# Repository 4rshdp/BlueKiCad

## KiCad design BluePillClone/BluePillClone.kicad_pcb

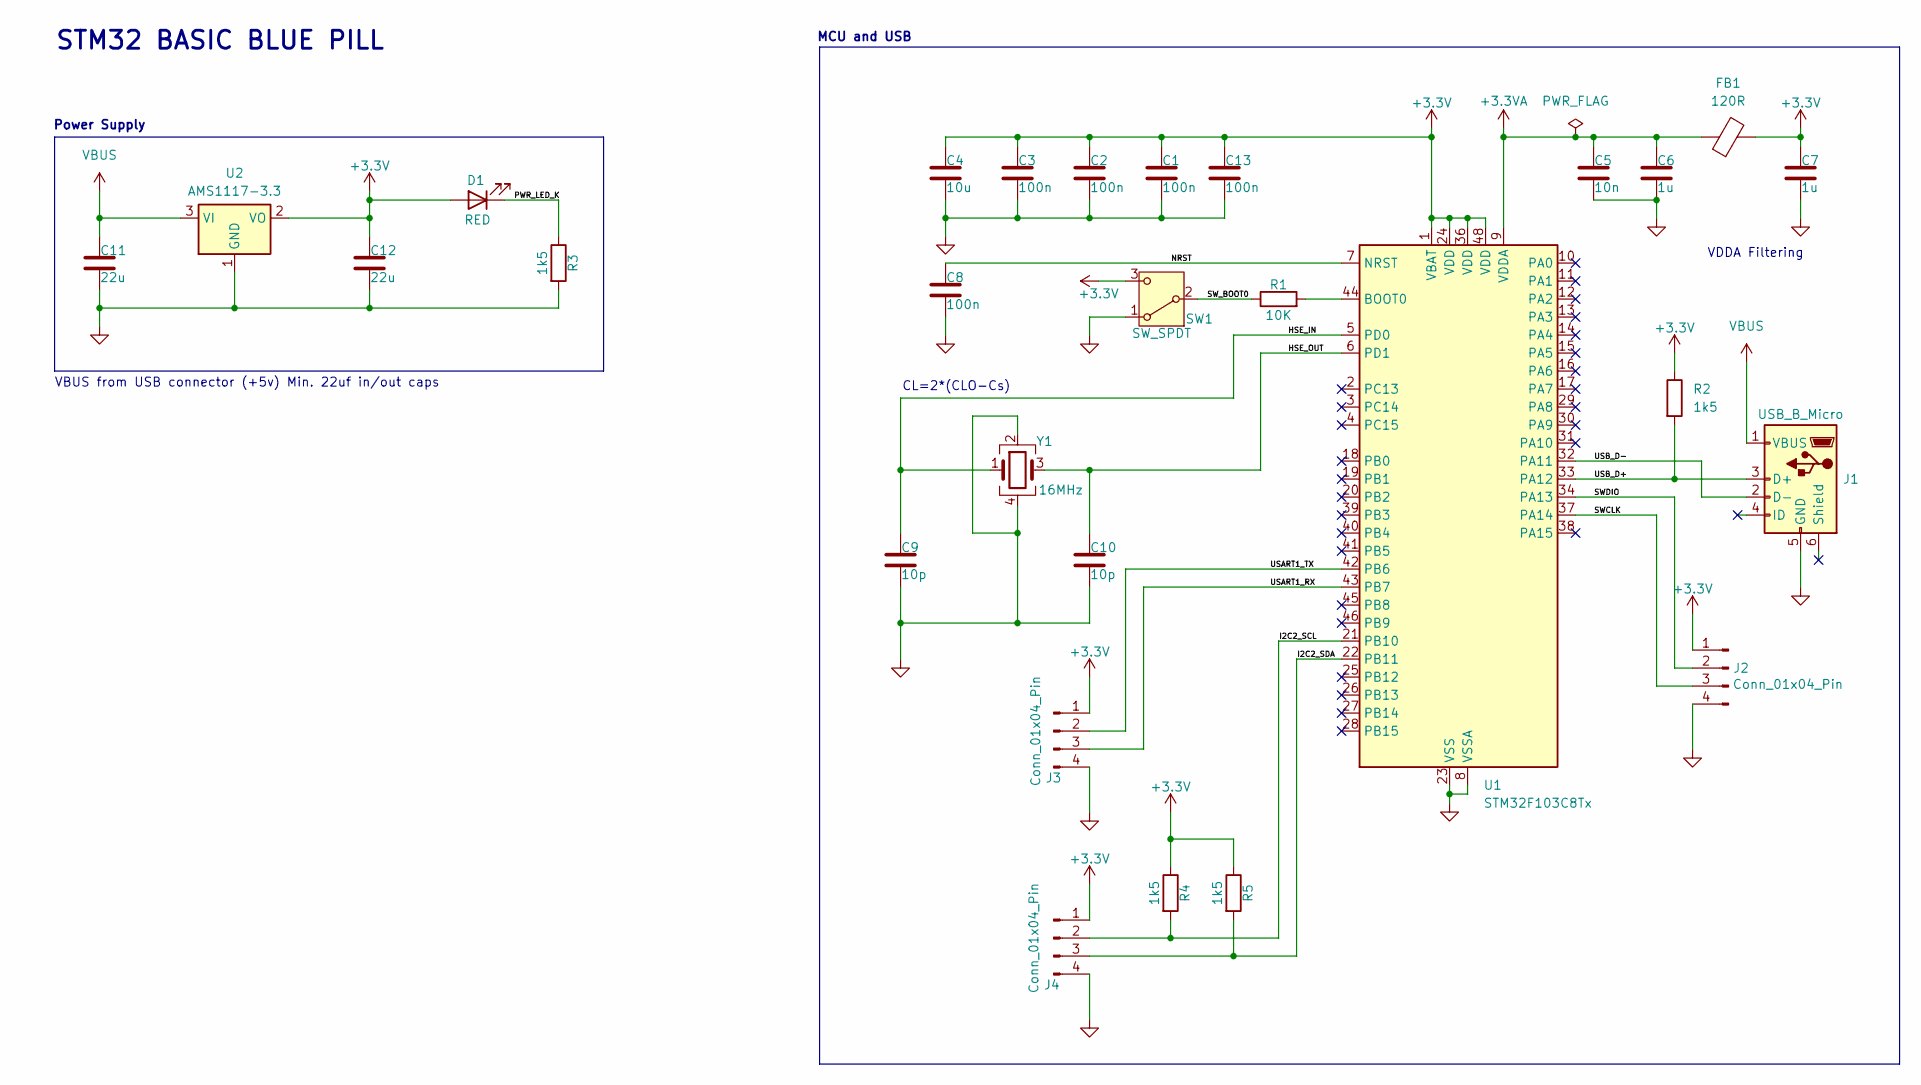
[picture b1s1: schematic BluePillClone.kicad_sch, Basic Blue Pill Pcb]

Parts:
C1, C2, C3, C8, C13: 100n; C_0402_1005Metric
C4: 10u; C_0402_1005Metric
C5: 10n; C_0402_1005Metric
C6, C7: 1u; C_0402_1005Metric
C9, C10: 10p; C_0402_1005Metric
C11, C12: 22u; C_0805_2012Metric
D1: RED; LED_0603_1608Metric
FB1: 120R; L_0603_1608Metric
J1: USB_B_Micro; USB_Micro-B_Wuerth_629105150521
J2, J3, J4: Conn_01x04_Pin; PinHeader_1x04_P2.54mm_Vertical
R1: 10K; R_01005_0402Metric
R2, R3, R4, R5: 1k5; R_01005_0402Metric
SW1: SW_SPDT; SW_Push_1P2T_Vertical_E-Switch_800UDP8P1A1M6
U1: STM32F103C8Tx; LQFP-48_7x7mm_P0.5mm
U2: AMS1117-3.3; SOT-223-3_TabPin2
Y1: 16MHz; Crystal_SMD_3225-4Pin_3.2x2.5mm

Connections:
+3.3V: C1.1, C2.1, C3.1, C4.1, C7.1, C12.1, C13.1, D1.2 (A), FB1.2, J2.1, J3.1, J4.1, R2.1, R4.1, R5.1, SW1.3 (C), U1.1 (VBAT), U1.24 (VDD), U1.36 (VDD), U1.48 (VDD), U2.2 (VO)
+3.3VA: C5.1, C6.1, FB1.1, U1.9 (VDDA)
/HSE_IN: C9.1, U1.5 (PD0), Y1.1
/HSE_OUT: C10.1, U1.6 (PD1), Y1.3
/I2C2_SCL: J4.2, R4.2, U1.21 (PB10)
/I2C2_SDA: J4.3, R5.2, U1.22 (PB11)
/NRST: C8.1, U1.7 (NRST)
/PWR_LED_K: D1.1 (K), R3.1
/SWCLK: J2.3, U1.37 (PA14)
/SWDIO: J2.2, U1.34 (PA13)
/SW_BOOT0: R1.1, SW1.2 (B)
/USART1_RX: J3.3, U1.43 (PB7)
/USART1_TX: J3.2, U1.42 (PB6)
/USB_D+: J1.3 (D+), R2.2, U1.33 (PA12)
/USB_D-: J1.2 (D-), U1.32 (PA11)
GND: C1.2, C2.2, C3.2, C4.2, C5.2, C6.2, C7.2, C8.2, C9.2, C10.2, C11.2, C12.2, C13.2, J1.5 (GND), J2.4, J3.4, J4.4, R3.2, SW1.1 (A), U1.8 (VSSA), U1.23 (VSS), U1.35 (VSS), U1.47 (VSS), U2.1 (GND), Y1.2, Y1.4
unnamed: R1.2, U1.44 (BOOT0)
VBUS: C11.1, J1.1 (VBUS), U2.3 (VI)

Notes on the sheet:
MCU and USB
CL=2*(CLO-Cs)
VDDA Filtering
VBUS from USB connector (+5v) Min. 22uf in/out caps
Power Supply
STM32 BASIC BLUE PILL

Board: 2 copper layers, 28 parts (0 on the bottom side), 18 nets, no tracks yet.

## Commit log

2025-01-21 Schematic
2025-01-22 basic PCB components placement
2025-01-23 Final Commit.
    Got Bored Not continuing further.
    Routing needed to be done.
